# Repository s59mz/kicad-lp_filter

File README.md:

# kicad-lp_filter
Low pass filter for HF Power Amplifier

Schematic:
[low_pass.pdf](low_pass.pdf)

BOM:
[low_pass.csv](low_pass.csv)

Gerbers:
[gerbers.zip](https://github.com/s59mz/kicad-lp_filter/raw/main/gerbers.zip)

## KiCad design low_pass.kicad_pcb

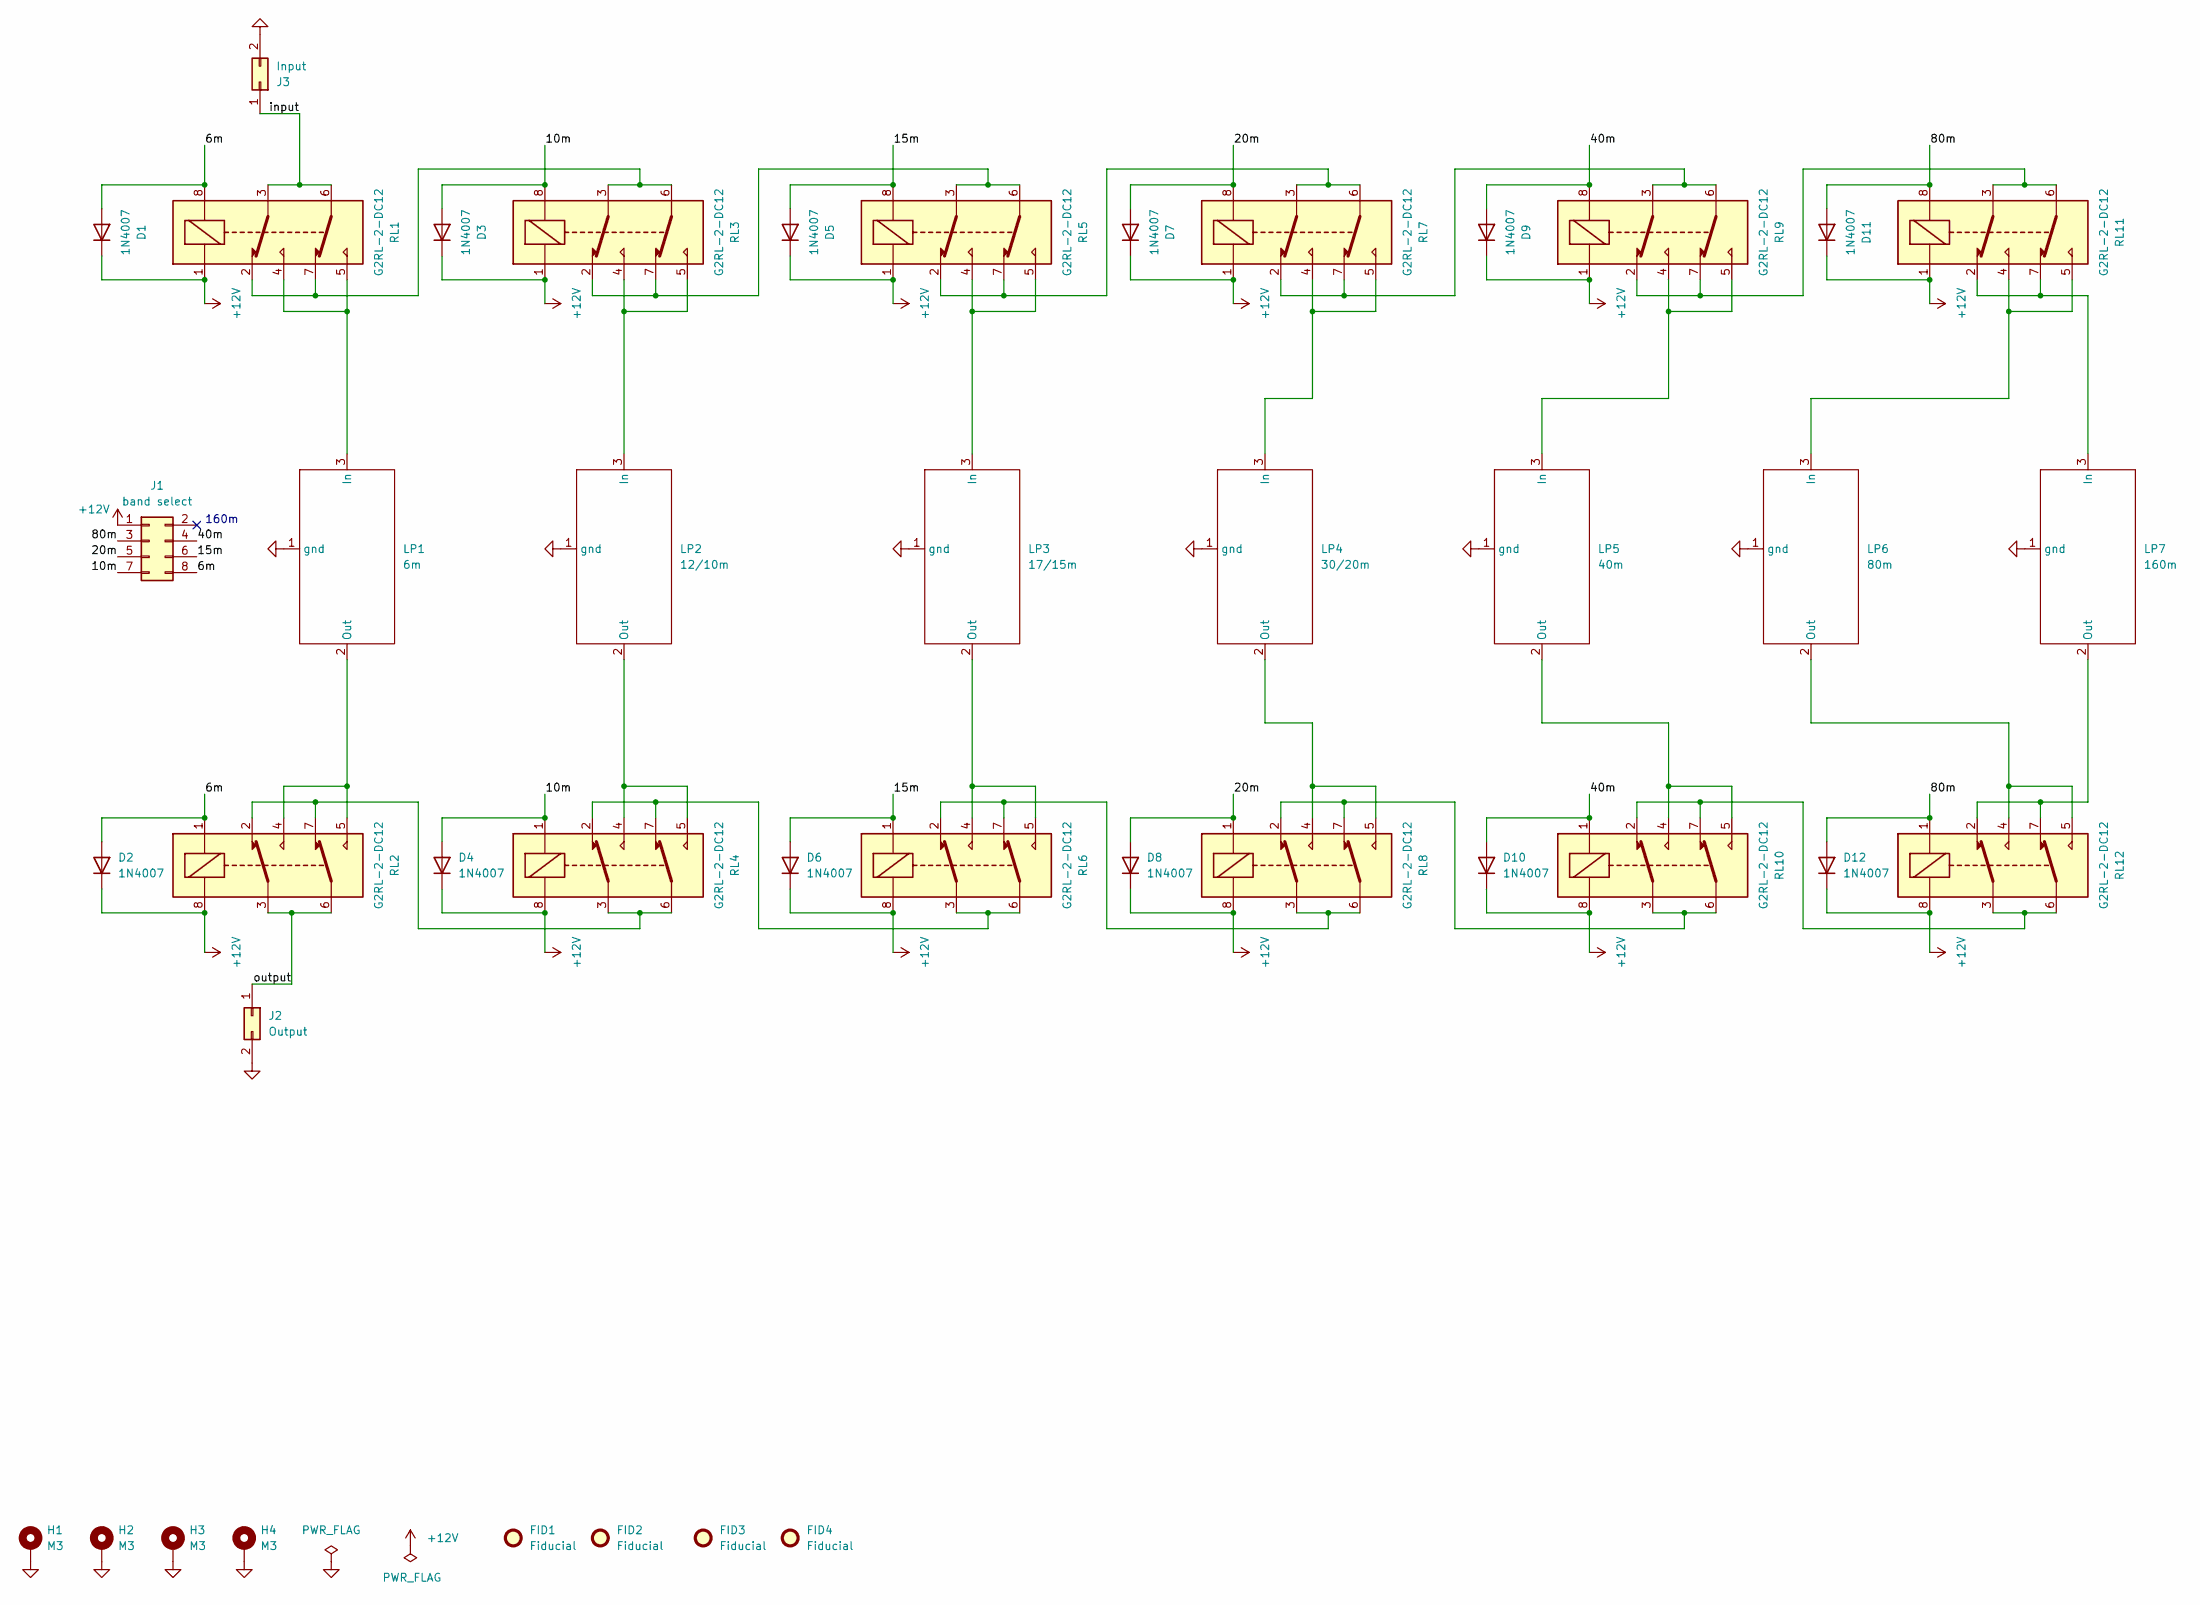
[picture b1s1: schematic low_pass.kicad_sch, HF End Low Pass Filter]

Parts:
D1, D2, D3, D4, D5, D6, D7, D8, D9, D10, D11, D12: 1N4007; D_SMB
FID1, FID2, FID3, FID4: Fiducial; Fiducial_1mm_Mask2mm
H1, H2, H3, H4: M3; MountingHole_3.2mm_M3_DIN965_Pad
J1: band select; PinHeader_2x04_P2.54mm_Vertical
J2: Output; Coax_terminal
J3: Input; Coax_terminal
LP1: 6m; LPF-6
LP2: 12/10m; LPF-6
LP3: 17/15m; LPF
LP4: 30/20m; LPF
LP5: 40m; LPF
LP6: 80m; LPF
LP7: 160m; LPF
RL1, RL2, RL3, RL4, RL5, RL6, RL7, RL8, RL9, RL10, RL11, RL12: G2RL-2-DC12; Relay_DPDT_Omron_G2RL

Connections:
+12V: D1.1 (K), D2.1 (K), D3.1 (K), D4.1 (K), D5.1 (K), D6.1 (K), D7.1 (K), D8.1 (K), D9.1 (K), D10.1 (K), D11.1 (K), D12.1 (K), J1.1, RL1.1, RL2.8, RL3.1, RL4.8, RL5.1, RL6.8, RL7.1, RL8.8, RL9.1, RL10.8, RL11.1, RL12.8
/6m: D1.2 (A), D2.2 (A), J1.8, RL1.8, RL2.1
/10m: D3.2 (A), D4.2 (A), J1.7, RL3.8, RL4.1
/15m: D5.2 (A), D6.2 (A), J1.6, RL5.8, RL6.1
/20m: D7.2 (A), D8.2 (A), J1.5, RL7.8, RL8.1
/40m: D9.2 (A), D10.2 (A), J1.4, RL9.8, RL10.1
/80m: D11.2 (A), D12.2 (A), J1.3, RL11.8, RL12.1
/input: J3.1, RL1.3, RL1.6
/output: J2.1, RL2.3, RL2.6
GND: H1.1, H2.1, H3.1, H4.1, J2.2, J3.2, LP1.1 (gnd), LP2.1 (gnd), LP3.1 (gnd), LP4.1 (gnd), LP5.1 (gnd), LP6.1 (gnd), LP7.1 (gnd)
unnamed: LP1.2 (Out), RL2.4, RL2.5
unnamed: LP1.3 (In), RL1.4, RL1.5
unnamed: LP2.2 (Out), RL4.4, RL4.5
unnamed: LP2.3 (In), RL3.4, RL3.5
unnamed: LP3.2 (Out), RL6.4, RL6.5
unnamed: LP3.3 (In), RL5.4, RL5.5
unnamed: LP4.2 (Out), RL8.4, RL8.5
unnamed: LP4.3 (In), RL7.4, RL7.5
unnamed: LP5.2 (Out), RL10.4, RL10.5
unnamed: LP5.3 (In), RL9.4, RL9.5
unnamed: LP6.2 (Out), RL12.4, RL12.5
unnamed: LP6.3 (In), RL11.4, RL11.5
unnamed: LP7.2 (Out), RL12.2, RL12.7
unnamed: LP7.3 (In), RL11.2, RL11.7
unnamed: RL1.2, RL1.7, RL3.3, RL3.6
unnamed: RL2.2, RL2.7, RL4.3, RL4.6
unnamed: RL3.2, RL3.7, RL5.3, RL5.6
unnamed: RL4.2, RL4.7, RL6.3, RL6.6
unnamed: RL5.2, RL5.7, RL7.3, RL7.6
unnamed: RL6.2, RL6.7, RL8.3, RL8.6
unnamed: RL7.2, RL7.7, RL9.3, RL9.6
unnamed: RL10.2, RL10.7, RL12.3, RL12.6
unnamed: RL8.2, RL8.7, RL10.3, RL10.6
unnamed: RL9.2, RL9.7, RL11.3, RL11.6

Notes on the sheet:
160m

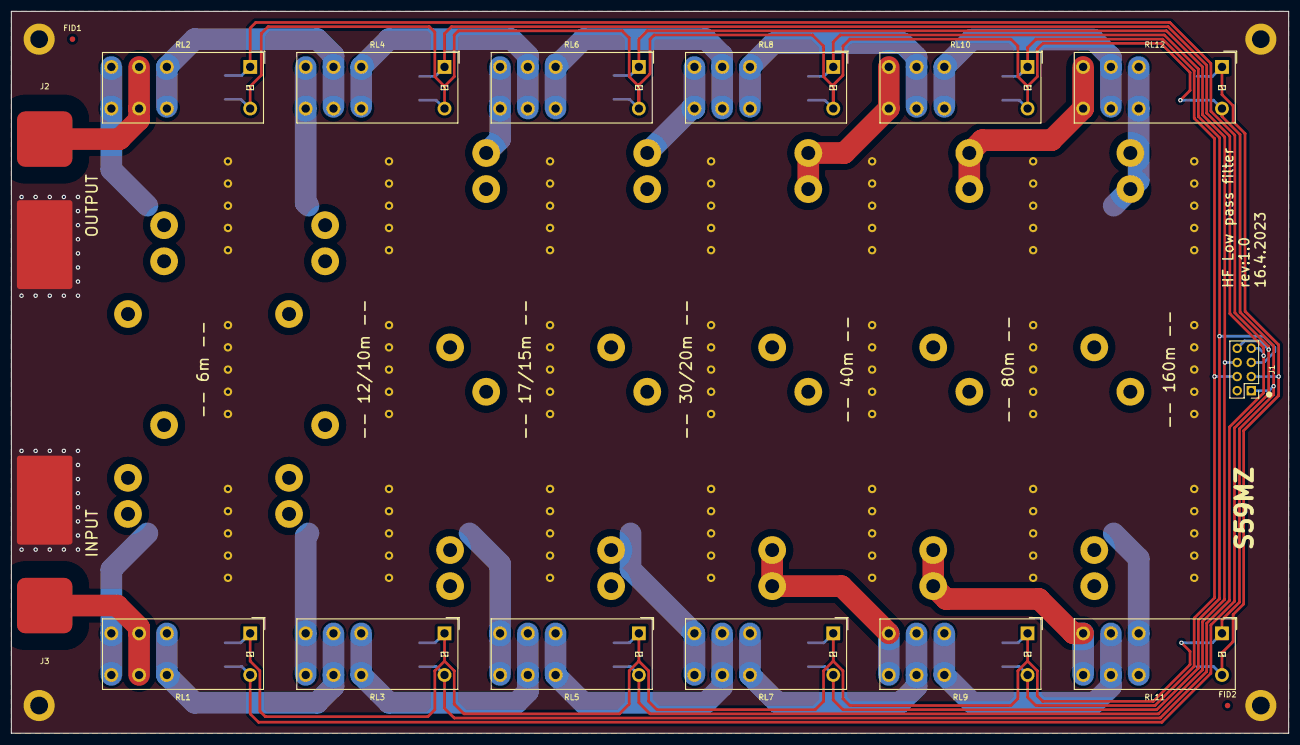
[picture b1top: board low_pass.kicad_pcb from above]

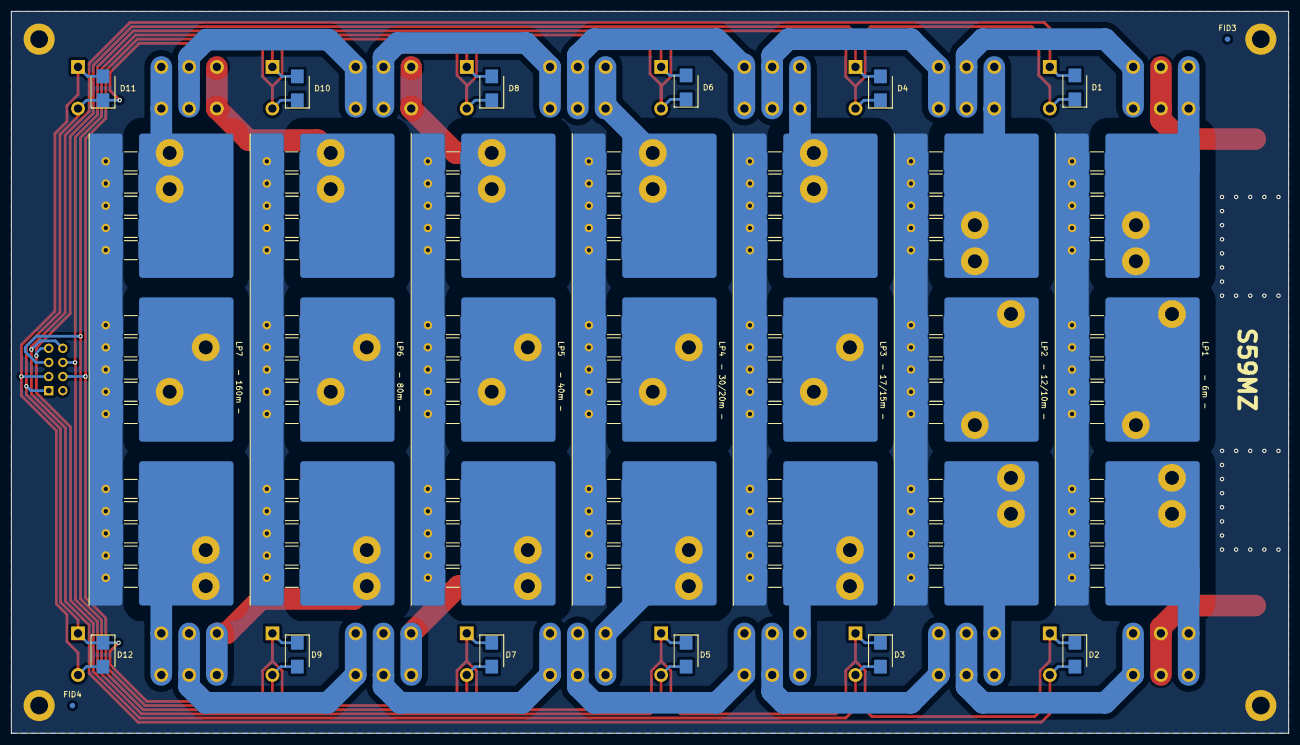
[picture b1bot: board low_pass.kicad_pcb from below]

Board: 2 copper layers, 230.0 x 130.0 mm, 42 parts (21 on the bottom side), 34 nets.
